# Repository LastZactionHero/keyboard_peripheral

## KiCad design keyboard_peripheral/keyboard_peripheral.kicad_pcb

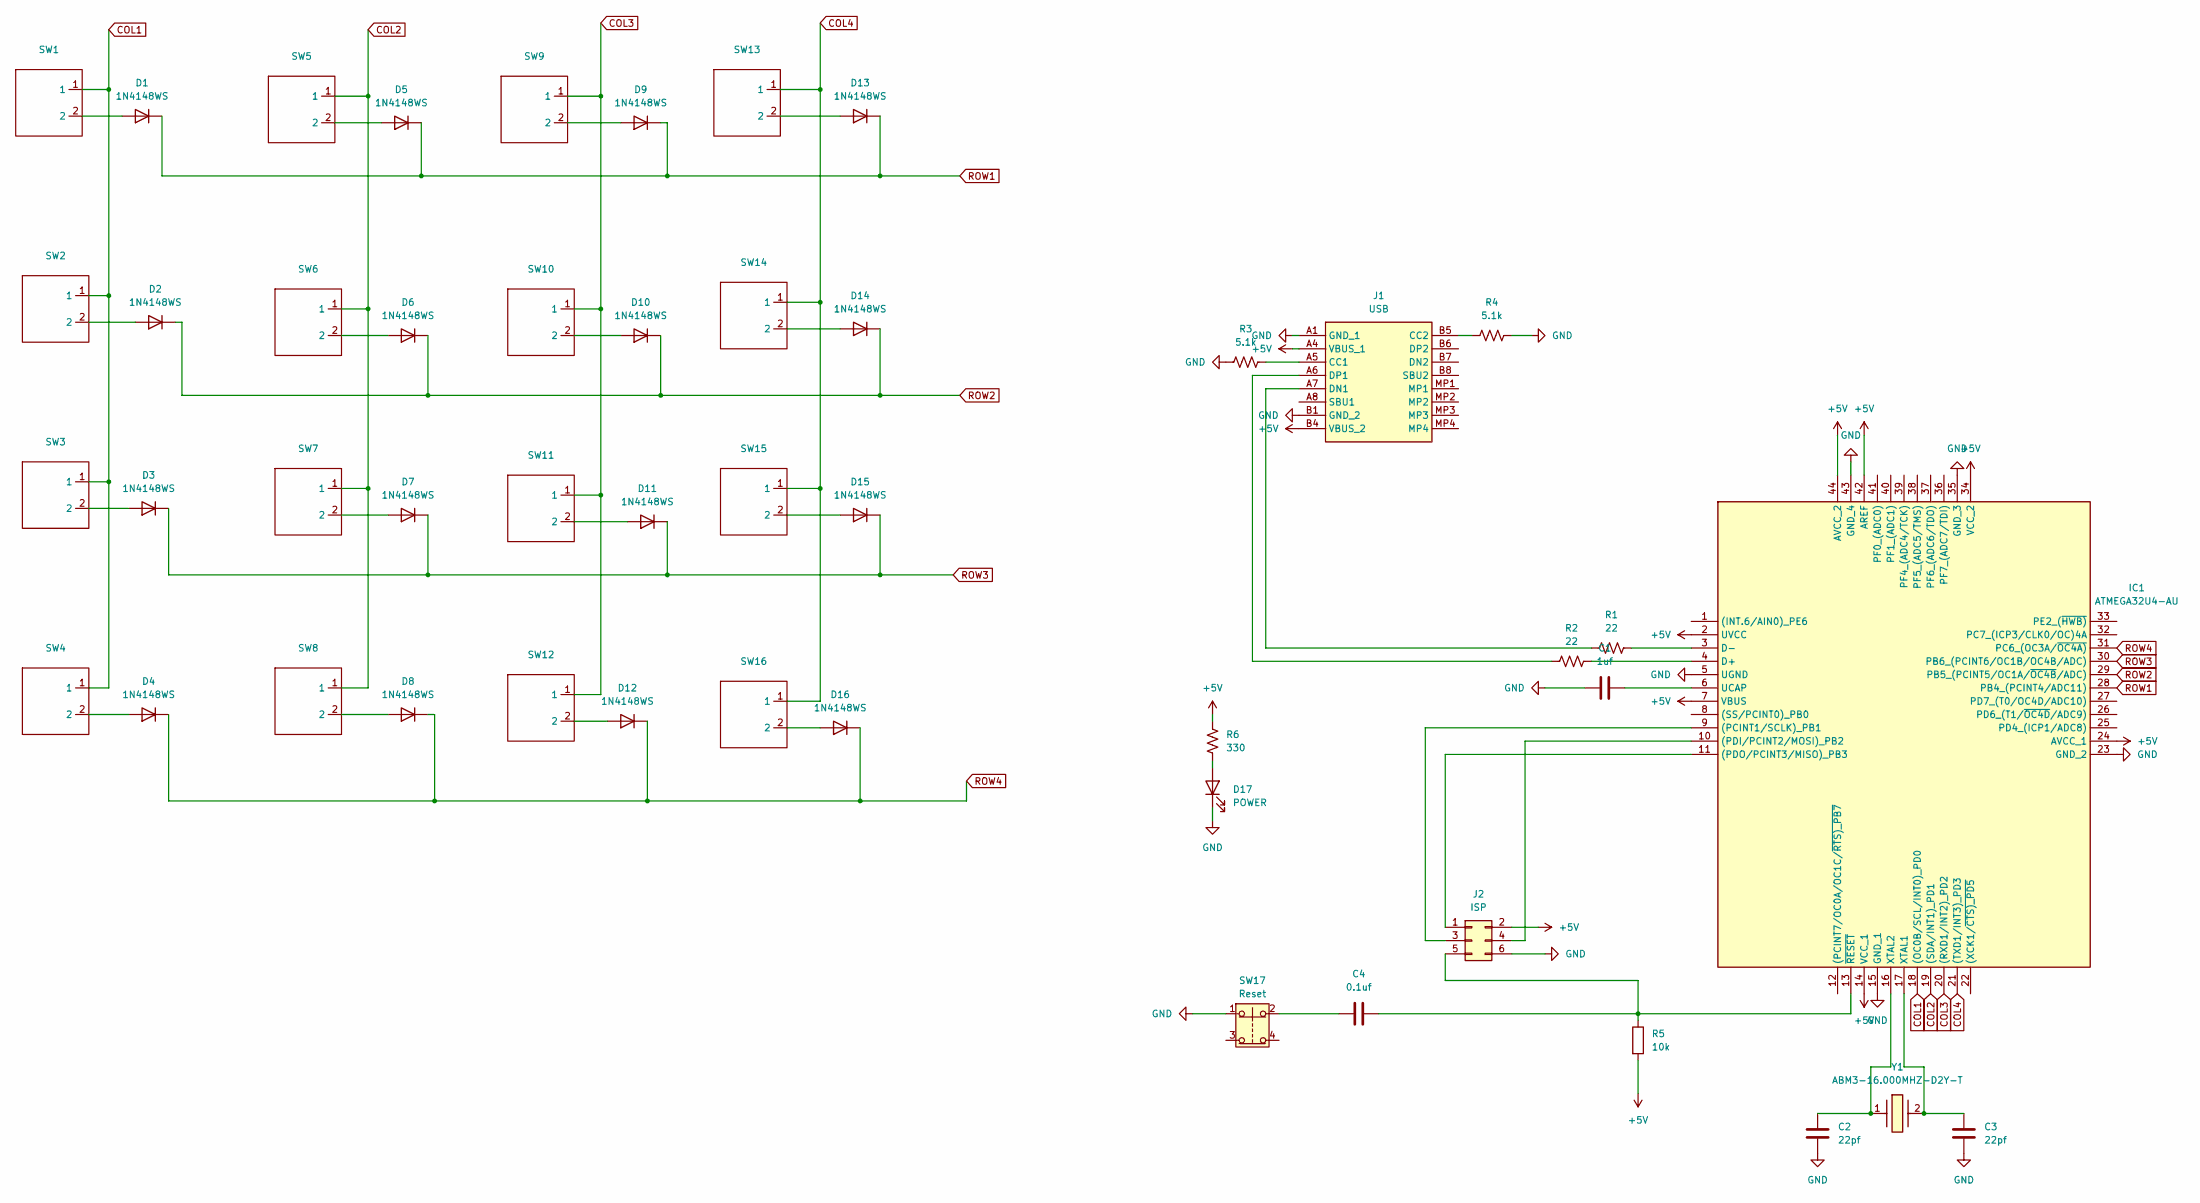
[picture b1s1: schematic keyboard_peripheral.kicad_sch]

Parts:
C1: 1uf; C_0805_2012Metric
C2, C3: 22pf; C_0805_2012Metric
C4: 0.1uf; C_0805_2012Metric
D1, D2, D3, D4, D5, D6, D7, D8, D9, D10, D11, D12, D13, D14, D15, D16: 1N4148WS; D_SOD-323
D17: POWER; LED_0201_0603Metric
IC1: ATMEGA32U4-AU; QFP80P1200X1200X120-44N; Mouser Part Number 556-ATMEGA32U4-AU
J1: USB; UJ20CHGSMT5P16TR; Mouser Part Number 179-UJ20CHGSMT5P16TR
J2: ISP; PinHeader_2x03_P2.54mm_Vertical
R1, R2: 22; R_0805_2012Metric
R3, R4: 5.1k; R_0805_2012Metric
R5: 10k; R_0805_2012Metric
R6: 330; R_0805_2012Metric
SW1, SW2, SW3, SW4, SW5, SW6, SW7, SW8, SW9, SW10, SW11, SW12, SW13, SW14, SW15, SW16: CherryMX_1.00u_PCB
SW17: Reset; SW_MEC_5GSH9
Y1: ABM3-16.000MHZ-D2Y-T; ABM3; Mouser Part Number 815-ABM3-16-D2Y-T

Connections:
+5V: IC1.2 (UVCC), IC1.7 (VBUS), IC1.14 (VCC_1), IC1.24 (AVCC_1), IC1.34 (VCC_2), IC1.42 (AREF), IC1.44 (AVCC_2), J1.A4 (VBUS_1), J1.B4 (VBUS_2), J2.2, R5.2, R6.1
COL1: IC1.18 ((OC0B/SCL/INT0)_PD0), SW1.1, SW2.1, SW3.1, SW4.1
COL2: IC1.19 ((SDA/INT1)_PD1), SW5.1, SW6.1, SW7.1, SW8.1
COL3: IC1.20 ((RXD1/INT2)_PD2), SW9.1, SW10.1, SW11.1, SW12.1
COL4: IC1.21 ((TXD1/INT3)_PD3), SW13.1, SW14.1, SW15.1, SW16.1
GND: C1.1, C2.2, C3.2, D17.1 (K), IC1.5 (UGND), IC1.15 (GND_1), IC1.23 (GND_2), IC1.35 (GND_3), IC1.43 (GND_4), J1.A1 (GND_1), J1.B1 (GND_2), J2.6, R3.1, R4.2, SW17.1
unnamed: C4.2, SW17.2
unnamed: D1.2 (A), SW1.2
unnamed: D2.2 (A), SW2.2
unnamed: D3.2 (A), SW3.2
unnamed: D4.2 (A), SW4.2
unnamed: D5.2 (A), SW5.2
unnamed: D6.2 (A), SW6.2
unnamed: D7.2 (A), SW7.2
unnamed: D8.2 (A), SW8.2
unnamed: D9.2 (A), SW9.2
unnamed: D10.2 (A), SW10.2
unnamed: D11.2 (A), SW11.2
unnamed: D12.2 (A), SW12.2
unnamed: D13.2 (A), SW13.2
unnamed: D14.2 (A), SW14.2
unnamed: D15.2 (A), SW15.2
unnamed: D16.2 (A), SW16.2
unnamed: D17.2 (A), R6.2
unnamed: IC1.9 ((PCINT1/SCLK)_PB1), J2.3
unnamed: IC1.10 ((PDI/PCINT2/MOSI)_PB2), J2.4
unnamed: IC1.11 ((PDO/PCINT3/MISO)_PB3), J2.1
unnamed: IC1.4 (D+), R2.2
unnamed: IC1.3 (D-), R1.2
unnamed: C1.2, IC1.6 (UCAP)
unnamed: C3.1, IC1.17 (XTAL1), Y1.2
unnamed: C2.1, IC1.16 (XTAL2), Y1.1
unnamed: C4.1, IC1.13 (~RESET), J2.5, R5.1
unnamed: J1.A5 (CC1), R3.2
unnamed: J1.B5 (CC2), R4.1
unnamed: J1.A7 (DN1), R1.1
unnamed: J1.A6 (DP1), R2.1
ROW1: D1.1 (K), D5.1 (K), D9.1 (K), D13.1 (K), IC1.28 (PB4_(PCINT4/ADC11))
ROW2: D2.1 (K), D6.1 (K), D10.1 (K), D14.1 (K), IC1.29 (PB5_(PCINT5/OC1A/~OC4B/ADC))
ROW3: D3.1 (K), D7.1 (K), D11.1 (K), D15.1 (K), IC1.30 (PB6_(PCINT6/OC1B/OC4B/ADC))
ROW4: D4.1 (K), D8.1 (K), D12.1 (K), D16.1 (K), IC1.31 (PC6_(OC3A/~OC4A))

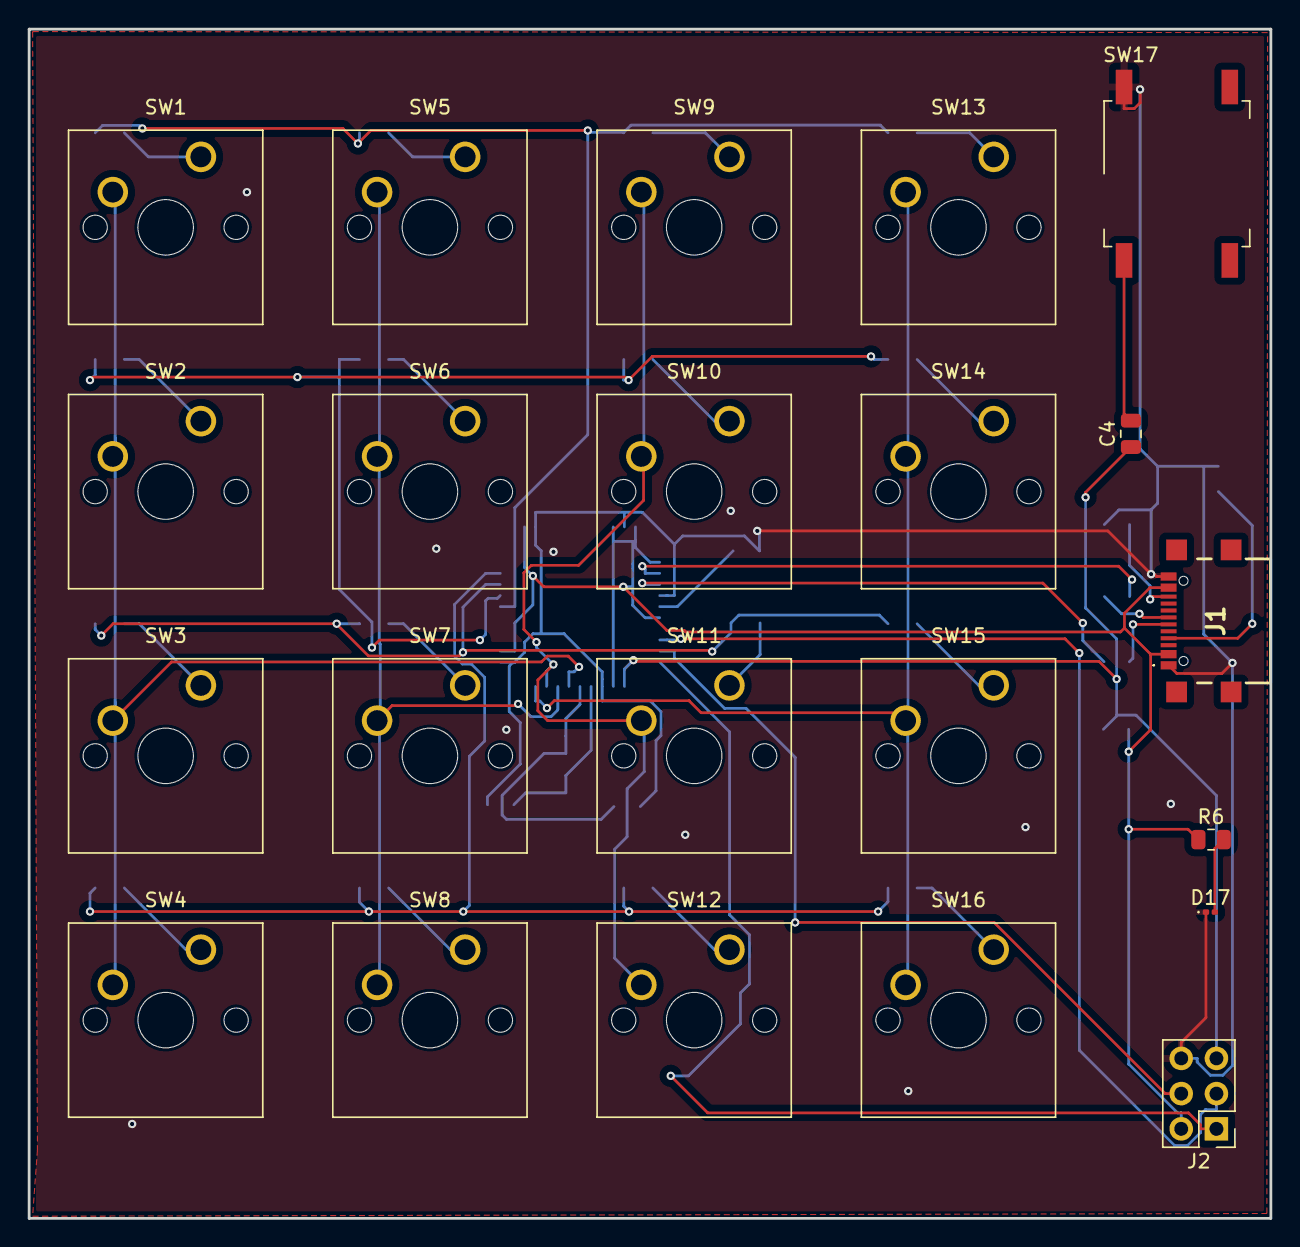
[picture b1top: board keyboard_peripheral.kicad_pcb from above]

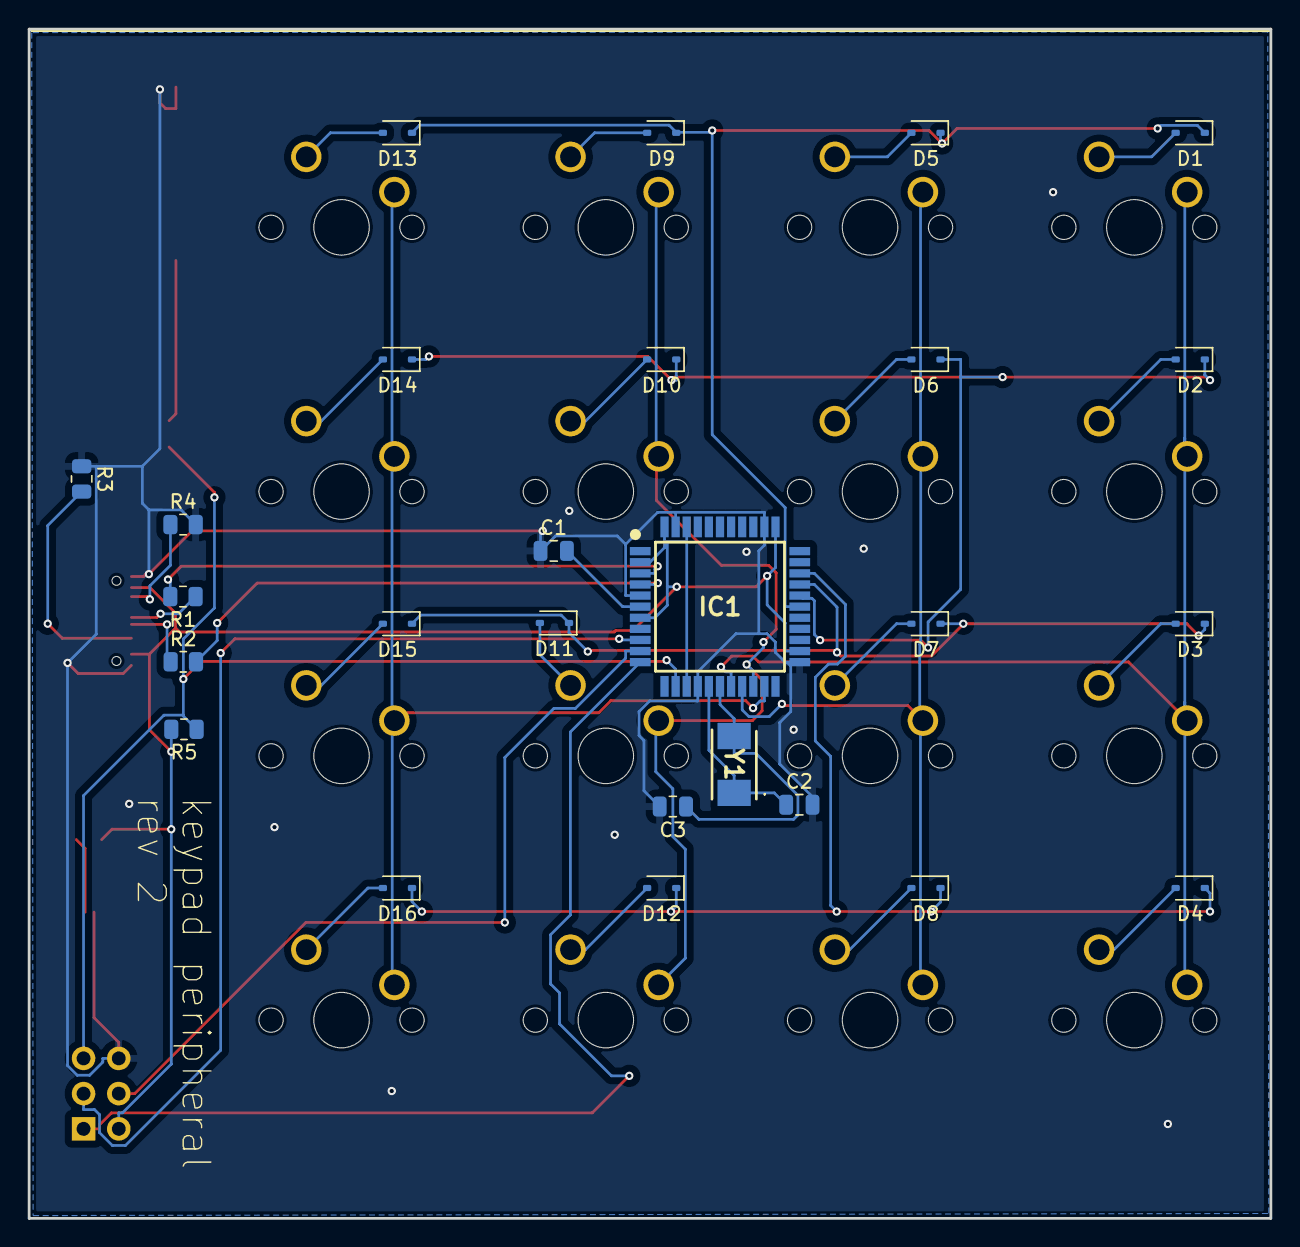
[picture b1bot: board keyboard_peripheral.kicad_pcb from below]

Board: 2 copper layers, 89.5 x 85.7 mm, 48 parts (26 on the bottom side), 41 nets.

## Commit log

2025-05-02 Add LED; Unroute
2025-05-02 rerouting
